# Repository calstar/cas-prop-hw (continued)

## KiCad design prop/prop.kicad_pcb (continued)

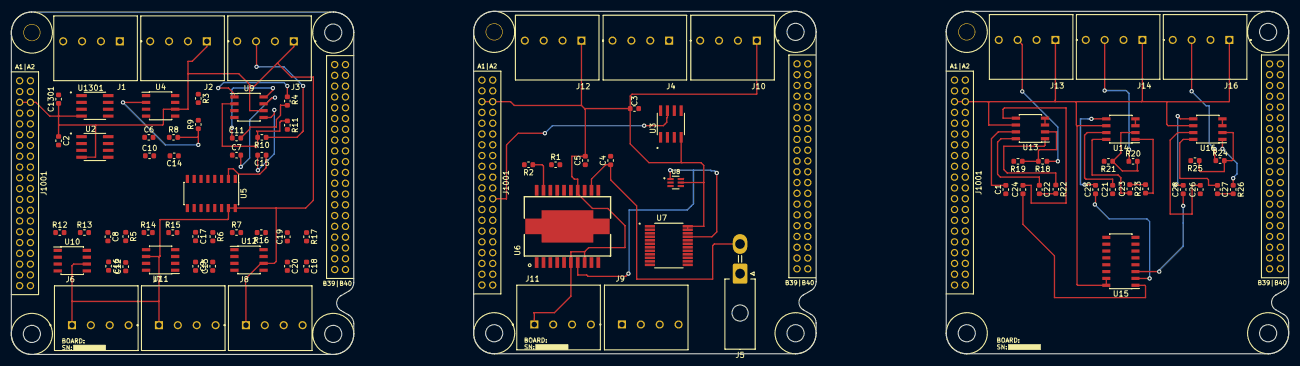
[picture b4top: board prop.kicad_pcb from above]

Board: 2 copper layers, 236.9 x 63.6 mm, 89 parts (0 on the bottom side), 141 nets.

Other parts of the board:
C2, C3, C1301: 0.1u; C_0603_1608Metric
J1001, J1001#2, J1001#3: CAS_stacking; CAS_physical
U2, U3, U1301: MAX6675ISA+; SOIC127P600X175-8N

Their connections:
+3V3: J1001.A35, J1001.A36, J1001#2.A35, J1001#2.A36, J1001#3.A35, J1001#3.A36; also elsewhere on the board
+5V: C2.1, C3.1, C1301.1, J1001.A5, J1001.A6, J1001#2.A5, J1001#2.A6, J1001#3.A5, J1001#3.A6, U2.4, U3.4, U1301.4; also elsewhere on the board
+BATT: J1001.A39, J1001.A40, J1001#2.A39, J1001#2.A40, J1001#3.A39, J1001#3.A40
/CS1: J1001.A21, J1001#2.A21, J1001#3.A21; also elsewhere on the board
/CS2: J1001.A22, J1001#2.A22, J1001#3.A22, U1301.6
/CS3: J1001.A23, J1001#2.A23, J1001#3.A23, U2.6
/CS4: J1001.A25, J1001#2.A25, J1001#3.A25, U3.6
/CS5: J1001.A27, J1001#2.A27, J1001#3.A27; also elsewhere on the board
/MAX6675ISA+/T+: U1301.3; also elsewhere on the board
/PWM1_33: J1001.A1, J1001#2.A1, J1001#3.A1; also elsewhere on the board
/PWM2_33: J1001.A2, J1001#2.A2, J1001#3.A2; also elsewhere on the board
/PWM3_33: J1001.A9, J1001#2.A9, J1001#3.A9; also elsewhere on the board
/SPI0_MISO: J1001.A24, J1001#2.A24, J1001#3.A24, U2.7, U3.7, U1301.7
/SPIO_MOSI: J1001.A28, J1001#2.A28, J1001#3.A28; also elsewhere on the board
/SPIO_SCK: J1001.A32, J1001#2.A32, J1001#3.A32, U2.5, U3.5, U1301.5
/Sol1_33: J1001.A10, J1001#2.A10, J1001#3.A10; also elsewhere on the board
/Sol2_33: J1001.A11, J1001#2.A11, J1001#3.A11; also elsewhere on the board
/sheet605A8BD6/I2C0_SCL: J1001.A13, J1001#2.A13, J1001#3.A13
/sheet605A8BD6/I2C0_SDA: J1001.A14, J1001#2.A14, J1001#3.A14
/sheet605A8BD6/I2C1_SCL: J1001.A17, J1001#2.A17, J1001#3.A17
/sheet605A8BD6/I2C1_SDA: J1001.A18, J1001#2.A18, J1001#3.A18
/sheet605A8BD6/INT6: J1001.A12, J1001#2.A12, J1001#3.A12
/sheet605A8BD6/INT7: J1001.A19, J1001#2.A19, J1001#3.A19
/sheet605A8BD6/INT8: J1001.A20, J1001#2.A20, J1001#3.A20
/sheet605A8BD6/SPI0_nSS6: J1001.A29, J1001#2.A29, J1001#3.A29
/sheet605A8BD6/SPI0_nSS7: J1001.A31, J1001#2.A31, J1001#3.A31
/sheet605A8BD6/SPI0_nSS8: J1001.A33, J1001#2.A33, J1001#3.A33
/sheet605A8BD6/SPIHS_MISO: J1001.B5, J1001#2.B5, J1001#3.B5
/sheet605A8BD6/SPIHS_MOSI: J1001.B9, J1001#2.B9, J1001#3.B9
/sheet605A8BD6/SPIHS_SCK: J1001.B2, J1001#2.B2, J1001#3.B2
/sheet605A8BD6/SPIHS_nSS1: J1001.B13, J1001#2.B13, J1001#3.B13
/sheet605A8BD6/SPIHS_nSS2: J1001.B14, J1001#2.B14, J1001#3.B14
/sheet6059AC1E/T+: U2.3; also elsewhere on the board
/sheet6059B70A/T+: U3.3; also elsewhere on the board
GND: C2.2, C3.2, C1301.2, J1001.A3, J1001.A4, J1001.A7, J1001.A8, J1001.A15, J1001.A16, J1001.A26, J1001.A30, J1001.A34, J1001.A37, J1001.A38, J1001.B1, J1001.B3, J1001.B4, J1001.B6, J1001.B7, J1001.B8, J1001.B10, J1001.B11, J1001.B12, J1001#2.A3, J1001#2.A4, J1001#2.A7, J1001#2.A8, J1001#2.A15, J1001#2.A16, J1001#2.A26, J1001#2.A30, J1001#2.A34, J1001#2.A37, J1001#2.A38, J1001#2.B1, J1001#2.B3, J1001#2.B4, J1001#2.B6, J1001#2.B7, J1001#2.B8, J1001#2.B10, J1001#2.B11, J1001#2.B12, J1001#3.A3, J1001#3.A4, J1001#3.A7, J1001#3.A8, J1001#3.A15, J1001#3.A16, J1001#3.A26, J1001#3.A30, J1001#3.A34, J1001#3.A37, J1001#3.A38, J1001#3.B1, J1001#3.B3, J1001#3.B4, J1001#3.B6, J1001#3.B7, J1001#3.B8, J1001#3.B10, J1001#3.B11, J1001#3.B12, U2.1, U2.2, U3.1, U3.2, U1301.1, U1301.2; also elsewhere on the board
unnamed: J1001.B15, J1001#2.B15, J1001#3.B15
unnamed: J1001.B16, J1001#2.B16, J1001#3.B16
unnamed: J1001.B17, J1001#2.B17, J1001#3.B17
unnamed: J1001.B18, J1001#2.B18, J1001#3.B18
unnamed: J1001.B19, J1001#2.B19, J1001#3.B19
unnamed: J1001.B20, J1001#2.B20, J1001#3.B20
unnamed: J1001.B21, J1001#2.B21, J1001#3.B21
unnamed: J1001.B22, J1001#2.B22, J1001#3.B22
unnamed: J1001.B23, J1001#2.B23, J1001#3.B23
unnamed: J1001.B24, J1001#2.B24, J1001#3.B24
unnamed: J1001.B25, J1001#2.B25, J1001#3.B25
unnamed: J1001.B26, J1001#2.B26, J1001#3.B26
unnamed: J1001.B27, J1001#2.B27, J1001#3.B27
unnamed: J1001.B28, J1001#2.B28, J1001#3.B28
unnamed: J1001.B29, J1001#2.B29, J1001#3.B29
unnamed: J1001.B30, J1001#2.B30, J1001#3.B30
unnamed: J1001.B31, J1001#2.B31, J1001#3.B31
unnamed: J1001.B32, J1001#2.B32, J1001#3.B32
unnamed: J1001.B33, J1001#2.B33, J1001#3.B33
unnamed: J1001.B34, J1001#2.B34, J1001#3.B34
unnamed: J1001.B35, J1001#2.B35, J1001#3.B35
unnamed: J1001.B36, J1001#2.B36, J1001#3.B36
unnamed: J1001.B37, J1001#2.B37, J1001#3.B37
unnamed: J1001.B38, J1001#2.B38, J1001#3.B38
unnamed: J1001.B39, J1001#2.B39, J1001#3.B39
unnamed: J1001.B40, J1001#2.B40, J1001#3.B40

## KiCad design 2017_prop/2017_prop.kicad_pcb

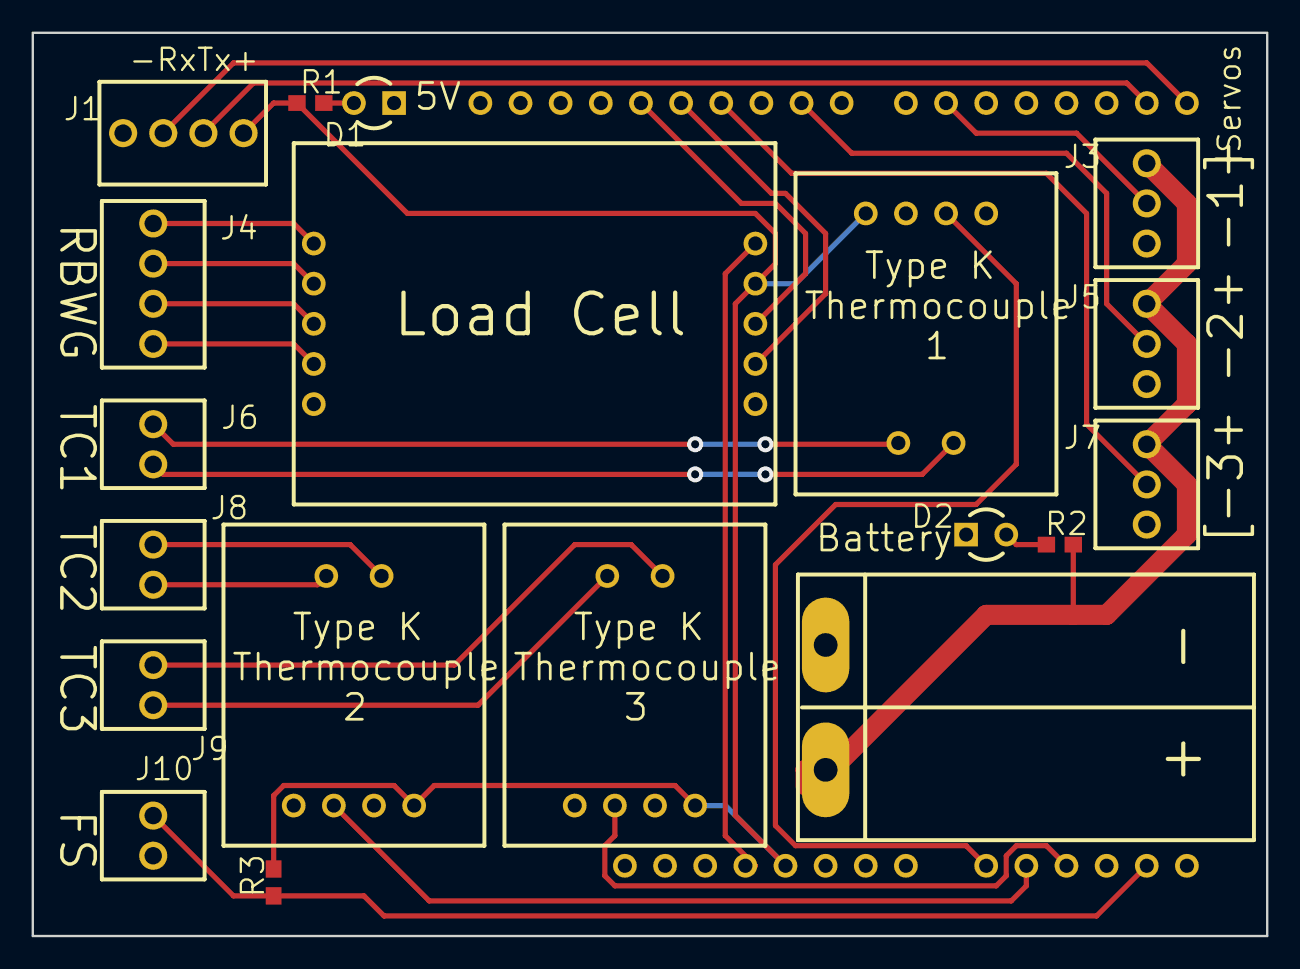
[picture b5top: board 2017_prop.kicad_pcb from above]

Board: 2 copper layers, 78.1 x 57.1 mm, 20 parts (0 on the bottom side), 19 nets.

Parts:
B1: SOURCE_BATTERY2; PowerPole_45A_Adjacent
D1: DIO_LED_1; LED-3R_Red
D2: DIO_LED_1; LED-3R_Red_D2
J1: EJECTIONINTERFACE; 282834-4
J2: ARDUINO; ArduinoShield
J3, J5, J7: SERVO; 282834-3
J4: LOADCELL; 282834-4_J4
J6: THERMOCOUPLE; 282834-2
J8: THERMOCOUPLE; 282834-2_J8
J9: THERMOCOUPLE; 282834-2_J9
J10: FLOWSWITCH; 282834-2_J10
R1: 150; RES_0603
R2: 315; RES_0603_R2
R3: 10k; RES_0603_R2
U1: HX711BREAKOUT; HX711Breakout
U2, U3, U4: AD8495BREAKOUT; AD8495Breakout

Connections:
1: J2.7, J2.10, J2.12, J2.13, J2.14, J2.20, J2.22, J2.23, J2.24, J3.2, J5.2, J7.2, J10.1, R3.1, U1.7, U1.8, U2.3, U3.3, U4.3
+3V3: J2.29, U1.10
+5V: J1.1, J2.28, R1.2, R3.2, U1.9, U2.1, U3.1, U4.1
+V: B1.2, J3.1, J5.1, J7.1, R2.2
GND: B1.1, D1.1, D2.1, J1.4, J2.15, J2.26, J2.27, J3.3, J5.3, J7.3, J10.2, U1.6, U2.2, U2.4, U3.2, U3.4, U4.2, U4.4
unnamed: D1.2, R1.1
unnamed: D2.2, R2.1
unnamed: J1.2, J2.2
unnamed: J1.3, J2.1
unnamed: J4.1, U1.1
unnamed: J4.2, U1.2
unnamed: J4.3, U1.3
unnamed: J4.4, U1.4
unnamed: J6.1, U2.6
unnamed: J6.2, U2.5
unnamed: J8.1, U3.6
unnamed: J8.2, U3.5
unnamed: J9.1, U4.6
unnamed: J9.2, U4.5

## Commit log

2021-01-30 Setup
2021-01-30 old prop kicad
2021-02-27 new commit
2021-02-28 some changes
2021-02-28 smaller capacitors
2021-03-05 changed load cell to have 4 pins
2021-03-07 added ADC and amplifier
2021-03-14 updated amplifier, added hierarchical sheets
2021-03-15 updated SCK
2021-03-17 imported cas-bus schematic
2021-03-27 schematic updated, very rough layout
2021-04-07 split board into 3
2021-04-16 updated schematic
2021-04-20 more updates to layout
2021-04-21 started routing
2021-04-23 changed to 4 layer board
2021-04-23 more layout progress on 4 layer board
2021-04-28 working on left board
2021-04-30 more layout on middle board
2021-04-30 mostly done with routing on all 3 boards
2021-05-01 made gerbers
2022-01-23 split into 3 schematic sheets
2022-01-25 Prop_PCB_1 done
2022-01-25 Prop_PCB_1 fix
2022-01-30 Prop_PCB_2 and Prop_PCB_3 done
2022-01-30 finalize3pcb schematic
2022-02-02 fix spelling errors in signals
2022-02-11 PCB_3 layout ongoing
2022-02-11 rearranged the pcb to be more neat
2022-02-21 finished routing
2022-02-25 fixed outstanding routing errors
2022-02-28 Connected power wires.
2022-02-28 added STAR and BCA logos
2022-03-02 Almost finished wiring PCB.
2022-03-04 added silkscreen labels
2022-03-06 Passed DRC (kind of).
2022-03-06 Set minimum clearance to 0.25 mm.
2022-03-06 Updated hard-sch-blocks
2022-03-07 Added Star, BAC logo.
2022-03-07 made spacing equal for both sides
2022-03-07 Added front/back ground pour.
2022-03-07 finalized board
2022-03-07 Fixed power pours.
2022-03-11 Shorted U1 to GND.
2022-03-14 Done rewiring.
2022-03-14 Removed unconnected lines.
2022-03-14 Fixed unconnected GND pin.
